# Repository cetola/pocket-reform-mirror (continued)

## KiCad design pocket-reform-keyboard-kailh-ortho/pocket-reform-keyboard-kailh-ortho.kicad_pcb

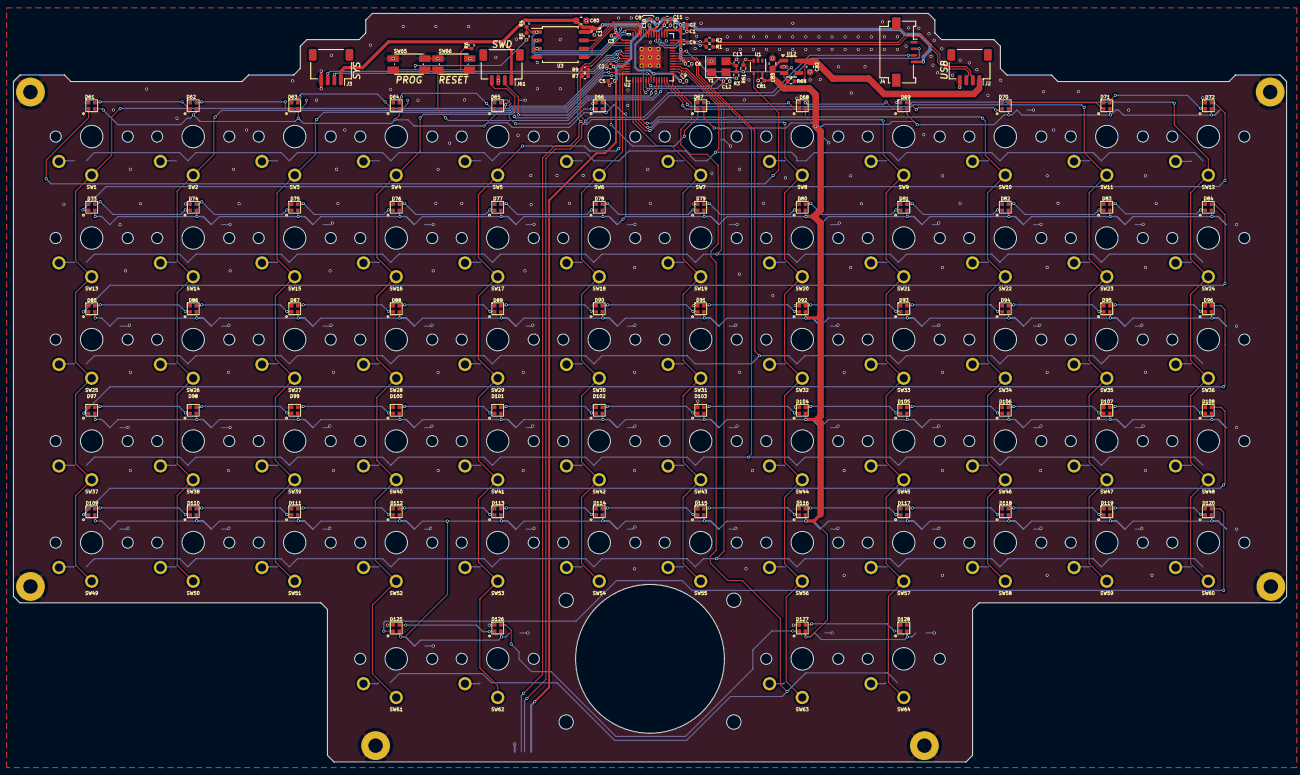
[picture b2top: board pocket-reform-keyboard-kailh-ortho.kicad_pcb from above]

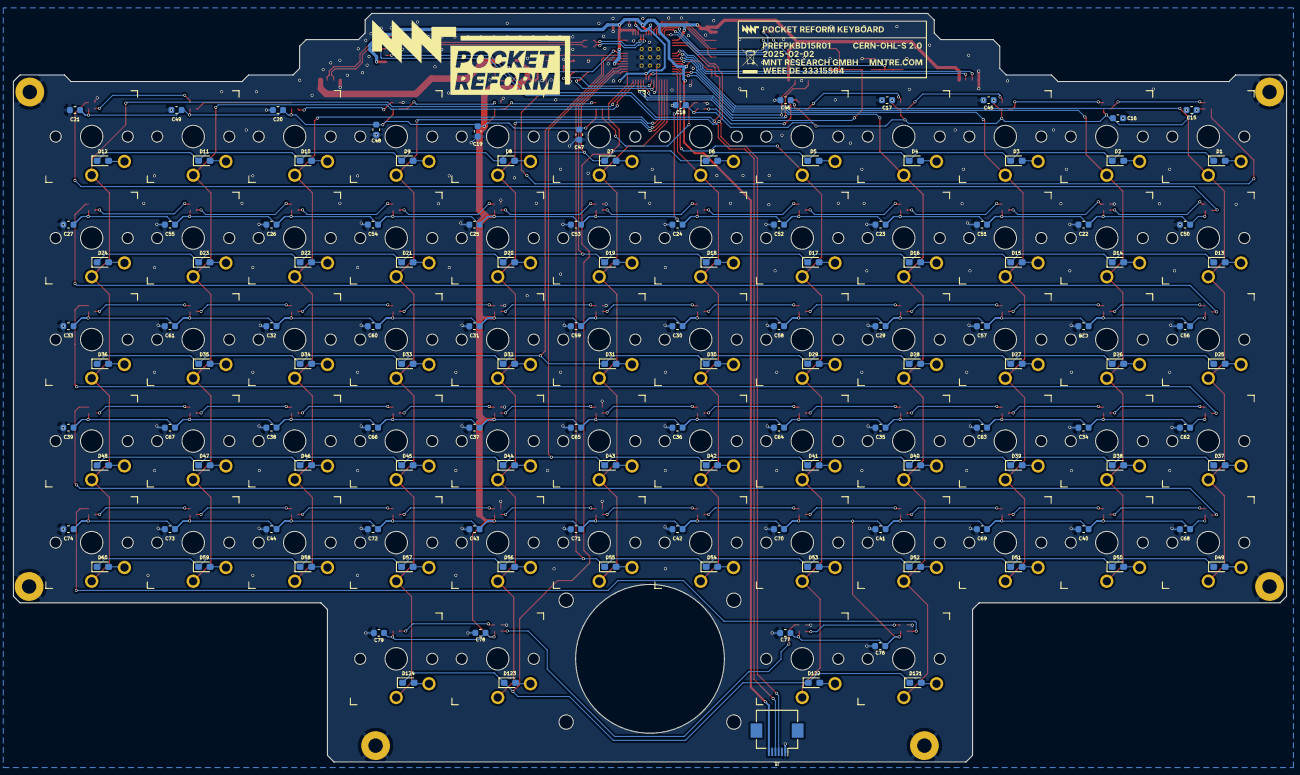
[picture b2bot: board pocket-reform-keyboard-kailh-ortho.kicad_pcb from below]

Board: 4 copper layers, 194.4 x 114.3 mm, 309 parts (131 on the bottom side), 175 nets.

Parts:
C1, C2, C3, C4, C5, C6, C8, C9, C10, C11, C14, C81: 0.1uF; C_0402_1005Metric
C7, C75: 1uF; C_0402_1005Metric
C12, C13: 15pF; C_0402_1005Metric
C15, C16, C17, C18, C19, C20, C21, C22, C23, C24, C25, C26, C27, C28, C29, C30, C31, C32, C33, C34, C35, C36, C37, C38, C39, C40, C41, C42, C43, C44, C45, C46, C47, C48, C49, C50, C51, C52, C53, C54, C55, C56, C57, C58, C59, C60, C61, C62, C63, C64, C65, C66, C67, C68, C69, C70, C71, C72, C73, C74, C76, C77, C78, C79: 0.1uF; C_0603_1608Metric
C80, C82, C83: 10uF; C_0603_1608Metric
D1, D2, D3, D4, D5, D6, D7, D8, D9, D10, D11, D12, D13, D14, D15, D16, D17, D18, D19, D20, D21, D22, D23, D24, D25, D26, D27, D28, D29, D30, D31, D32, D33, D34, D35, D36, D37, D38, D39, D40, D41, D42, D43, D44, D45, D46, D47, D48, D49, D50, D51, D52, D53, D54, D55, D56, D57, D58, D59, D60, D121, D122, D123, D124: MMDL914T1G; D_0603_1608Metric_Pad1.05x0.95mm_HandSolder
D61, D62, D63, D64, D65, D66, D67, D68, D69, D70, D71, D72, D73, D74, D75, D76, D77, D78, D79, D80, D81, D82, D83, D84, D85, D86, D87, D88, D89, D90, D91, D92, D93, D94, D95, D96, D97, D98, D99, D100, D101, D102, D103, D104, D105, D106, D107, D108, D109, D110, D111, D112, D113, D114, D115, D116, D117, D118, D119, D120, D125, D126, D127, D128: SK6805-EC15
GFX1: MNT; pocket-reform
GFX2: MNT; pref-keyboard15-badge
H1: MH1; MountingHole_2.2mm_M2_Pad
H2: MH2; MountingHole_2.2mm_M2_Pad
H3: MH3; MountingHole_2.2mm_M2_Pad
H4: MH4; MountingHole_2.2mm_M2_Pad
H5: MH5; MountingHole_2.2mm_M2_Pad
H6: MH6; MountingHole_2.2mm_M2_Pad
H7, H8, H9, H10: TBH; MountingHole_2.2mm_M2
J1: Conn_01x06_Female; Hirose_FH12-6S-0.5SH_1x06-1MP_P0.50mm_Horizontal
J2: USB; JST_SH_SM04B-SRSS-TB_1x04-1MP_P1.00mm_Horizontal
J3, J61: UART; JST_SH_SM04B-SRSS-TB_1x04-1MP_P1.00mm_Horizontal
J4: AUX; Molex_200528-0040_1x04-1MP_P1.00mm_Horizontal
R1, R2: 27.4; R_0402_1005Metric
R3, R5: 1k; R_0402_1005Metric
R4, R6, R61, R68: 10k; R_0402_1005Metric
R7, R9: 4.7k; R_0402_1005Metric
SW1, SW2, SW3, SW4, SW5, SW6, SW7, SW8, SW9, SW10, SW11, SW12, SW13, SW14, SW15, SW16, SW17, SW18, SW19, SW20, SW21, SW22, SW23, SW24, SW25, SW26, SW27, SW28, SW29, SW30, SW31, SW32, SW33, SW34, SW35, SW36, SW37, SW38, SW39, SW40, SW41, SW42, SW43, SW44, SW45, SW46, SW47, SW48, SW49, SW50, SW51, SW52, SW53, SW54, SW55, SW56, SW57, SW58, SW59, SW60, SW61, SW62, SW63, SW64: Choc; PG1350
SW65: SW_HWB; Diptronics-PTLP2
SW66: SW_RST; Diptronics-PTLP2
U1: SN74LV1T34DCK; SOT-353_SC-70-5
U2: RP2040; RP2040-QFN-56
U3: W25Q32JVSS; SOIC-8_5.23x5.23mm_P1.27mm
U12: AP22815A; SOT-23-5
Y1: 12MHz 12pF; Crystal_SMD_3225-4Pin_3.2x2.5mm

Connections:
+1V1: C9.1, C10.1, C11.1, C75.1, U2.23 (DVDD), U2.45 (VREG_VOUT), U2.50 (DVDD)
+3V3: C1.1, C2.1, C3.1, C4.1, C5.1, C6.1, C7.1, C8.1, C14.1, C80.1, J1.6, J3.1, J4.4, J61.1, R4.1, R6.1, R7.2, R9.2, U2.1 (IOVDD), U2.10 (IOVDD), U2.22 (IOVDD), U2.33 (IOVDD), U2.42 (IOVDD), U2.43 (ADC_AVDD), U2.44 (VREG_IN), U2.48 (USB_VDD), U2.49 (IOVDD), U3.8 (VCC)
+5V: C82.1, J2.1, R68.2, U12.5 (IN)
/Pocket Reform KBD MCU/UD+: R1.2, U2.47 (USB_DP)
/Pocket Reform KBD MCU/UD-: R2.1, U2.46 (USB_DM)
COL1: SW1.1, SW13.1, SW25.1, SW37.1, SW49.1, U2.8 (GPIO6)
COL2: SW2.1, SW14.1, SW26.1, SW38.1, SW50.1, U2.9 (GPIO7)
COL3: SW3.1, SW15.1, SW27.1, SW39.1, SW51.1, U2.11 (GPIO8)
COL4: SW4.1, SW16.1, SW28.1, SW40.1, SW52.1, SW61.1, U2.12 (GPIO9)
COL5: SW5.1, SW17.1, SW29.1, SW41.1, SW53.1, SW62.1, U2.13 (GPIO10)
COL6: SW6.1, SW18.1, SW30.1, SW42.1, SW54.1, U2.14 (GPIO11)
COL7: SW7.1, SW19.1, SW31.1, SW43.1, SW55.1, U2.15 (GPIO12)
COL8: SW8.1, SW20.1, SW32.1, SW44.1, SW56.1, SW63.1, U2.16 (GPIO13)
COL9: SW9.1, SW21.1, SW33.1, SW45.1, SW57.1, SW64.1, U2.17 (GPIO14)
COL10: SW10.1, SW22.1, SW34.1, SW46.1, SW58.1, U2.18 (GPIO15)
COL11: SW11.1, SW23.1, SW35.1, SW47.1, SW59.1, U2.27 (GPIO16)
COL12: SW12.1, SW24.1, SW36.1, SW48.1, SW60.1, U2.28 (GPIO17)
D+: J2.3, R1.1
D-: J2.2, R2.2
GND: C1.2, C2.2, C3.2, C4.2, C5.2, C6.2, C7.2, C8.2, C9.2, C10.2, C11.2, C12.2, C13.2, C14.2, C15.2, C16.2, C17.2, C18.2, C19.2, C20.2, C21.2, C22.2, C23.2, C24.2, C25.2, C26.2, C27.2, C28.2, C29.2, C30.2, C31.2, C32.2, C33.2, C34.2, C35.2, C36.2, C37.2, C38.2, C39.2, C40.2, C41.2, C42.2, C43.2, C44.2, C45.2, C46.2, C47.2, C48.2, C49.2, C50.2, C51.2, C52.2, C53.2, C54.2, C55.2, C56.2, C57.2, C58.2, C59.2, C60.2, C61.2, C62.2, C63.2, C64.2, C65.2, C66.2, C67.2, C68.2, C69.2, C70.2, C71.2, C72.2, C73.2, C74.2, C75.2, C76.2, C77.2, C78.2, C79.2, C80.2, C81.2, C82.2, C83.2, D61.4 (VSS), D62.4 (VSS), D63.4 (VSS), D64.4 (VSS), D65.4 (VSS), D66.4 (VSS), D67.4 (VSS), D68.4 (VSS), D69.4 (VSS), D70.4 (VSS), D71.4 (VSS), D72.4 (VSS), D73.4 (VSS), D74.4 (VSS), D75.4 (VSS), D76.4 (VSS), D77.4 (VSS), D78.4 (VSS), D79.4 (VSS), D80.4 (VSS), D81.4 (VSS), D82.4 (VSS), D83.4 (VSS), D84.4 (VSS), D85.4 (VSS), D86.4 (VSS), D87.4 (VSS), D88.4 (VSS), D89.4 (VSS), D90.4 (VSS), D91.4 (VSS), D92.4 (VSS), D93.4 (VSS), D94.4 (VSS), D95.4 (VSS), D96.4 (VSS), D97.4 (VSS), D98.4 (VSS), D99.4 (VSS), D100.4 (VSS), D101.4 (VSS), D102.4 (VSS), D103.4 (VSS), D104.4 (VSS), D105.4 (VSS), D106.4 (VSS), D107.4 (VSS), D108.4 (VSS), D109.4 (VSS), D110.4 (VSS), D111.4 (VSS), D112.4 (VSS), D113.4 (VSS), D114.4 (VSS), D115.4 (VSS), D116.4 (VSS), D117.4 (VSS), D118.4 (VSS), D119.4 (VSS), D120.4 (VSS), D125.4 (VSS), D126.4 (VSS), D127.4 (VSS), D128.4 (VSS), H1.1, H2.1, H3.1, H4.1, H5.1, H6.1, J1.1, J2.4, J3.4, J4.1, J61.3, R61.1, SW65.2, SW66.2, U1.3 (GND), U2.19 (TESTEN), U2.57 (GND), U3.4 (GND), U12.2 (GND), Y1.2, Y1.4
LED_DATA: U1.2 (A), U2.36 (GPIO24)
LED_POWER: C15.1, C16.1, C17.1, C18.1, C19.1, C20.1, C21.1, C22.1, C23.1, C24.1, C25.1, C26.1, C27.1, C28.1, C29.1, C30.1, C31.1, C32.1, C33.1, C34.1, C35.1, C36.1, C37.1, C38.1, C39.1, C40.1, C41.1, C42.1, C43.1, C44.1, C45.1, C46.1, C47.1, C48.1, C49.1, C50.1, C51.1, C52.1, C53.1, C54.1, C55.1, C56.1, C57.1, C58.1, C59.1, C60.1, C61.1, C62.1, C63.1, C64.1, C65.1, C66.1, C67.1, C68.1, C69.1, C70.1, C71.1, C72.1, C73.1, C74.1, C76.1, C77.1, C78.1, C79.1, C81.1, C83.1, D61.2 (VDD), D62.2 (VDD), D63.2 (VDD), D64.2 (VDD), D65.2 (VDD), D66.2 (VDD), D67.2 (VDD), D68.2 (VDD), D69.2 (VDD), D70.2 (VDD), D71.2 (VDD), D72.2 (VDD), D73.2 (VDD), D74.2 (VDD), D75.2 (VDD), D76.2 (VDD), D77.2 (VDD), D78.2 (VDD), D79.2 (VDD), D80.2 (VDD), D81.2 (VDD), D82.2 (VDD), D83.2 (VDD), D84.2 (VDD), D85.2 (VDD), D86.2 (VDD), D87.2 (VDD), D88.2 (VDD), D89.2 (VDD), D90.2 (VDD), D91.2 (VDD), D92.2 (VDD), D93.2 (VDD), D94.2 (VDD), D95.2 (VDD), D96.2 (VDD), D97.2 (VDD), D98.2 (VDD), D99.2 (VDD), D100.2 (VDD), D101.2 (VDD), D102.2 (VDD), D103.2 (VDD), D104.2 (VDD), D105.2 (VDD), D106.2 (VDD), D107.2 (VDD), D108.2 (VDD), D109.2 (VDD), D110.2 (VDD), D111.2 (VDD), D112.2 (VDD), D113.2 (VDD), D114.2 (VDD), D115.2 (VDD), D116.2 (VDD), D117.2 (VDD), D118.2 (VDD), D119.2 (VDD), D120.2 (VDD), D125.2 (VDD), D126.2 (VDD), D127.2 (VDD), D128.2 (VDD), U1.5 (VCC), U12.1 (OUT)
LED_PWR_EN: R61.2, U2.37 (GPIO25), U12.4 (EN)
unnamed: C13.1, R3.1, Y1.3
unnamed: D1.2 (A), SW1.2
unnamed: D2.2 (A), SW2.2
unnamed: D3.2 (A), SW3.2
unnamed: D4.2 (A), SW4.2
unnamed: D5.2 (A), SW5.2
unnamed: D6.2 (A), SW6.2
unnamed: D7.2 (A), SW7.2
unnamed: D8.2 (A), SW8.2
unnamed: D9.2 (A), SW9.2
unnamed: D10.2 (A), SW10.2
unnamed: D11.2 (A), SW11.2
unnamed: D12.2 (A), SW12.2
unnamed: D13.2 (A), SW13.2
unnamed: D14.2 (A), SW14.2
unnamed: D15.2 (A), SW15.2
unnamed: D16.2 (A), SW16.2
unnamed: D17.2 (A), SW17.2
unnamed: D18.2 (A), SW18.2
unnamed: D19.2 (A), SW19.2
unnamed: D20.2 (A), SW20.2
unnamed: D21.2 (A), SW21.2
unnamed: D22.2 (A), SW22.2
unnamed: D23.2 (A), SW23.2
unnamed: D24.2 (A), SW24.2
unnamed: D25.2 (A), SW25.2
unnamed: D26.2 (A), SW26.2
unnamed: D27.2 (A), SW27.2
unnamed: D28.2 (A), SW28.2
unnamed: D29.2 (A), SW29.2
unnamed: D30.2 (A), SW30.2
unnamed: D31.2 (A), SW31.2
unnamed: D32.2 (A), SW32.2
unnamed: D33.2 (A), SW33.2
unnamed: D34.2 (A), SW34.2
unnamed: D35.2 (A), SW35.2
unnamed: D36.2 (A), SW36.2
unnamed: D37.2 (A), SW37.2
unnamed: D38.2 (A), SW38.2
unnamed: D39.2 (A), SW39.2
unnamed: D40.2 (A), SW40.2
unnamed: D41.2 (A), SW41.2
unnamed: D42.2 (A), SW42.2
unnamed: D43.2 (A), SW43.2
unnamed: D44.2 (A), SW44.2
unnamed: D45.2 (A), SW45.2
unnamed: D46.2 (A), SW46.2
unnamed: D47.2 (A), SW47.2
unnamed: D48.2 (A), SW48.2
unnamed: D49.2 (A), SW49.2
unnamed: D50.2 (A), SW50.2
unnamed: D51.2 (A), SW51.2
unnamed: D52.2 (A), SW52.2
unnamed: D53.2 (A), SW53.2
unnamed: D54.2 (A), SW54.2
unnamed: D55.2 (A), SW55.2
unnamed: D56.2 (A), SW56.2
unnamed: D57.2 (A), SW57.2
unnamed: D58.2 (A), SW58.2
unnamed: D59.2 (A), SW59.2
unnamed: D60.2 (A), SW60.2
unnamed: D61.1 (DIN), U1.4 (Y)
unnamed: D61.3 (DOUT), D62.1 (DIN)
unnamed: D62.3 (DOUT), D63.1 (DIN)
unnamed: D63.3 (DOUT), D64.1 (DIN)
unnamed: D64.3 (DOUT), D65.1 (DIN)
unnamed: D65.3 (DOUT), D66.1 (DIN)
unnamed: D66.3 (DOUT), D67.1 (DIN)
unnamed: D67.3 (DOUT), D68.1 (DIN)
unnamed: D68.3 (DOUT), D69.1 (DIN)
unnamed: D69.3 (DOUT), D70.1 (DIN)
unnamed: D70.3 (DOUT), D71.1 (DIN)
unnamed: D71.3 (DOUT), D72.1 (DIN)
unnamed: D72.3 (DOUT), D73.1 (DIN)
unnamed: D73.3 (DOUT), D74.1 (DIN)
unnamed: D74.3 (DOUT), D75.1 (DIN)
unnamed: D75.3 (DOUT), D76.1 (DIN)
unnamed: D76.3 (DOUT), D77.1 (DIN)
unnamed: D77.3 (DOUT), D78.1 (DIN)
unnamed: D78.3 (DOUT), D79.1 (DIN)
unnamed: D79.3 (DOUT), D80.1 (DIN)
unnamed: D80.3 (DOUT), D81.1 (DIN)
unnamed: D81.3 (DOUT), D82.1 (DIN)
unnamed: D82.3 (DOUT), D83.1 (DIN)
unnamed: D83.3 (DOUT), D84.1 (DIN)
unnamed: D84.3 (DOUT), D85.1 (DIN)
unnamed: D85.3 (DOUT), D86.1 (DIN)
unnamed: D86.3 (DOUT), D87.1 (DIN)
unnamed: D87.3 (DOUT), D88.1 (DIN)
unnamed: D88.3 (DOUT), D89.1 (DIN)
unnamed: D89.3 (DOUT), D90.1 (DIN)
unnamed: D90.3 (DOUT), D91.1 (DIN)
unnamed: D91.3 (DOUT), D92.1 (DIN)
unnamed: D92.3 (DOUT), D93.1 (DIN)
unnamed: D93.3 (DOUT), D94.1 (DIN)
unnamed: D94.3 (DOUT), D95.1 (DIN)
unnamed: D95.3 (DOUT), D96.1 (DIN)
unnamed: D96.3 (DOUT), D97.1 (DIN)
unnamed: D97.3 (DOUT), D98.1 (DIN)
unnamed: D98.3 (DOUT), D99.1 (DIN)
unnamed: D99.3 (DOUT), D100.1 (DIN)
unnamed: D100.3 (DOUT), D101.1 (DIN)
unnamed: D101.3 (DOUT), D102.1 (DIN)
unnamed: D102.3 (DOUT), D103.1 (DIN)
unnamed: D103.3 (DOUT), D104.1 (DIN)
unnamed: D104.3 (DOUT), D105.1 (DIN)
unnamed: D105.3 (DOUT), D106.1 (DIN)
unnamed: D106.3 (DOUT), D107.1 (DIN)
unnamed: D107.3 (DOUT), D108.1 (DIN)
unnamed: D108.3 (DOUT), D109.1 (DIN)
unnamed: D109.3 (DOUT), D110.1 (DIN)
unnamed: D110.3 (DOUT), D111.1 (DIN)
unnamed: D111.3 (DOUT), D112.1 (DIN)
unnamed: D112.3 (DOUT), D113.1 (DIN)
unnamed: D113.3 (DOUT), D114.1 (DIN)
unnamed: D114.3 (DOUT), D115.1 (DIN)
unnamed: D115.3 (DOUT), D116.1 (DIN)
unnamed: D116.3 (DOUT), D117.1 (DIN)
unnamed: D117.3 (DOUT), D118.1 (DIN)
unnamed: D118.3 (DOUT), D119.1 (DIN)
unnamed: D119.3 (DOUT), D120.1 (DIN)
unnamed: D120.3 (DOUT), D125.1 (DIN)
unnamed: D121.2 (A), SW61.2
unnamed: D122.2 (A), SW62.2
unnamed: D123.2 (A), SW63.2
unnamed: D124.2 (A), SW64.2
unnamed: D125.3 (DOUT), D126.1 (DIN)
unnamed: D126.3 (DOUT), D127.1 (DIN)
unnamed: D127.3 (DOUT), D128.1 (DIN)
unnamed: C12.1, U2.20 (XIN), Y1.1
unnamed: R3.2, U2.21 (XOUT)
unnamed: R68.1, U12.3 (FLG)
PROG: R5.1, SW65.1
QSPI_CS: R4.2, R5.2, U2.56 (QSPI_SS), U3.1 (~CS)
QSPI_SCK: U2.52 (QSPI_SCLK), U3.6 (CLK)
QSPI_SD0: U2.53 (QSPI_SD0), U3.5 (DI(IO0))
QSPI_SD1: U2.55 (QSPI_SD1), U3.2 (DO(IO1))
QSPI_SD2: U2.54 (QSPI_SD2), U3.3 (IO2)
QSPI_SD3: U2.51 (QSPI_SD3), U3.7 (IO3)
RESET: R6.2, SW66.1, U2.26 (RUN)
ROW1: D1.1 (K), D2.1 (K), D3.1 (K), D4.1 (K), D5.1 (K), D6.1 (K), D7.1 (K), D8.1 (K), D9.1 (K), D10.1 (K), D11.1 (K), D12.1 (K), U2.30 (GPIO19)
ROW2: D13.1 (K), D14.1 (K), D15.1 (K), D16.1 (K), D17.1 (K), D18.1 (K), D19.1 (K), D20.1 (K), D21.1 (K), D22.1 (K), D23.1 (K), D24.1 (K), U2.31 (GPIO20)
ROW3: D25.1 (K), D26.1 (K), D27.1 (K), D28.1 (K), D29.1 (K), D30.1 (K), D31.1 (K), D32.1 (K), D33.1 (K), D34.1 (K), D35.1 (K), D36.1 (K), U2.35 (GPIO23)
ROW4: D37.1 (K), D38.1 (K), D39.1 (K), D40.1 (K), D41.1 (K), D42.1 (K), D43.1 (K), D44.1 (K), D45.1 (K), D46.1 (K), D47.1 (K), D48.1 (K), U2.34 (GPIO22)
ROW5: D49.1 (K), D50.1 (K), D51.1 (K), D52.1 (K), D53.1 (K), D54.1 (K), D55.1 (K), D56.1 (K), D57.1 (K), D58.1 (K), D59.1 (K), D60.1 (K), U2.32 (GPIO21)
ROW6: D121.1 (K), D122.1 (K), D123.1 (K), D124.1 (K), U2.29 (GPIO18)
SCL: J1.4, J4.3, R7.1, U2.3 (GPIO1)
SDA: J1.3, J4.2, R9.1, U2.2 (GPIO0)
SWC: J61.2, U2.24 (SWCLK)
SWD: J61.4, U2.25 (SWD)
UART_RX: J3.2, U2.7 (GPIO5)
UART_TX: J3.3, U2.6 (GPIO4)

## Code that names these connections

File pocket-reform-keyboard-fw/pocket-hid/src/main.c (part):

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  uart_set_format(UART_ID, DATA_BITS, STOP_BITS, PARITY);
  uart_set_hw_flow(UART_ID, false, false);
  uart_set_fifo_enabled(UART_ID, true);
  gpio_set_function(PIN_UART_TX, GPIO_FUNC_UART);
  gpio_set_function(PIN_UART_RX, GPIO_FUNC_UART);
  unsigned int UART_IRQ = UART_ID == uart0 ? UART0_IRQ : UART1_IRQ;

  gpio_init(PIN_LEDS);
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
  /* Configure rows as input and enable pull-downs */
  gpio_init_mask(PIN_ROW_MASK);
  gpio_pull_down(PIN_ROW1);
  gpio_pull_down(PIN_ROW2);
  gpio_pull_down(PIN_ROW3);
  gpio_pull_down(PIN_ROW4);
  gpio_pull_down(PIN_ROW5);
  gpio_pull_down(PIN_ROW6);

  i2c_init(i2c0, 400 * 1000);
  gpio_set_function(PIN_SDA, GPIO_FUNC_I2C);
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    uint32_t rows = 0;

    switch (x) {
    case 0: gpio_put(PIN_COL1, 1); break;
    case 1: gpio_put(PIN_COL2, 1); break;
    case 2: gpio_put(PIN_COL3, 1); break;
    case 3: gpio_put(PIN_COL4, 1); break;
    case 4: gpio_put(PIN_COL5, 1); break;
    case 5: gpio_put(PIN_COL6, 1); break;
    case 6: gpio_put(PIN_COL7, 1); break;
    case 7: gpio_put(PIN_COL8, 1); break;
    case 8: gpio_put(PIN_COL9, 1); break;
    case 9: gpio_put(PIN_COL10, 1); break;
    case 10: gpio_put(PIN_COL11, 1); break;
    case 11: gpio_put(PIN_COL12, 1); break;
    }

    // wait for signal to stabilize
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      uint8_t debounced_pressed = 0;

      switch (y) {
      case 0:  pressed = (rows & (1u<<PIN_ROW1)) != 0; break;
      case 1:  pressed = (rows & (1u<<PIN_ROW2)) != 0; break;
      case 2:  pressed = (rows & (1u<<PIN_ROW3)) != 0; break;
      case 3:  pressed = (rows & (1u<<PIN_ROW4)) != 0; break;
      case 4:  pressed = (rows & (1u<<PIN_ROW5)) != 0; break;
      case 5:  pressed = (rows & (1u<<PIN_ROW6)) != 0; break;
      }

      // shift new state as bit into debounce "register"
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
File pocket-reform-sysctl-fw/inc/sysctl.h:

#ifndef _POCKET_SYSCTL_H
#define _POCKET_SYSCTL_H

#include <stdint.h>

#include "pico/stdlib.h"
#include "pico/binary_info.h"
#include "hardware/i2c.h"
#include "hardware/spi.h"
#include "hardware/irq.h"
#include "hardware/rtc.h"
#include "hardware/clocks.h"
#include "hardware/pwm.h"
#include "hardware/watchdog.h"
#include "hardware/structs/watchdog.h"
#include "hardware/structs/vreg_and_chip_reset.h"

// #define OTG_AS_5V // WARNING: defining this requires the hardware mod described in https://source.mnt.re/reform/pocket-reform/-/issues/3
// #define FACTORY_MODE // turn device on immediately after starting sysctl
#define ACM_ENABLED // usb serial control for debugging

#define FW_STRING1 "PREF1SYS"
#define FW_STRING2 "R1"

#define PIN_SDA 0
#define PIN_SCL 1

#define PIN_DISP_RESET 2
#define PIN_FLIGHTMODE 3
#define PIN_KBD_UART_TX 4
#define PIN_KBD_UART_RX 5
#define PIN_WOWWAN 6
// TODO: FIXME: DISP_2_PWM on v20
#define PIN_DISP_EN 7
#define PIN_SOM_MOSI 8
#define PIN_SOM_SS0 9
#define PIN_SOM_SCK 10
#define PIN_SOM_MISO 11
#define PIN_SOM_UART_TX 12
#define PIN_SOM_UART_RX 13
#define PIN_FUSB_INT 14
#define PIN_LED_B 15
#define PIN_LED_B_PWM_SLICE 7
#define PIN_LED_B_PWM_CHAN PWM_CHAN_B
#define PIN_LED_R 16
#define PIN_LED_R_PWM_SLICE 0
#define PIN_LED_R_PWM_CHAN PWM_CHAN_A
#define PIN_LED_G 17
#define PIN_MODEM_POWER 18
#define PIN_SOM_WAKE 19
#define PIN_MODEM_RESET 20
#define PIN_1V1_ENABLE 23
// 3V3_ENABLE on v10, kickstart (power on button) DP HPD output on v20
#define PIN_3V3_ENABLE 24
#define PIN_V20_DP_HPD 24
// 5V_ENABLE on v10, kickstart (power on button) input on v20
#define PIN_5V_ENABLE 25
#define PIN_PHONE_DPR 27
// USB_SRC/PWREN_LATCH on v10, USB_SRC1/USB_SRC2 on v20
#define PIN_USB_SRC_ENABLE 28
#define PIN_USB_SRC1_ENABLE 28
#define PIN_PWREN_LATCH 29
#define PIN_USB_SRC2_ENABLE 29
// NC on v10, EDL/USB bootloader enable on v20
#define PIN_USB_LOADER_SW 26

// FUSB302B USB-PD controller
#define FUSB_ADDR 0x22
// MAX17320 protector/balancer
// https://datasheets.maximintegrated.com/en/ds/MAX17320.pdf
#define MAX_ADDR1 0x36
#define MAX_ADDR2 0x0b
// MP2650 charger
// https://www.monolithicpower.com/en/documentview/productdocument/index/version/2/document_type/Datasheet/lang/en/sku/MP2650GV/document_id/9664/
#define MPS_ADDR 0x5c
#define TMUX_ADDR 0x54
// PCA9536DP GPIO extender (for USWITCHes)
#define PCA9536_ADDR 0x41
// PCA9557PW GPIO extender
#define PCA9557_ADDR 0x19
// TODO eeprom: 0x50/0x58

#define I2C_TIMEOUT (1000 * 20)

#define UART_ID uart1
#define BAUD_RATE 115200
#define DATA_BITS 8
#define STOP_BITS 1
#define PARITY UART_PARITY_NONE

#define BOOT_MAGIC_2 0xAA55F0F0
#define BOOT_MAGIC_3 0x0F0F55AA
#define BOOT_MAGIC_OFF (io_rw_32)(-1)
// for remembering critical settings across warm resets
#define BOOT_SCRATCH_BITS0_IDX 1
// if this bit is set, we assume display v2 (for display_v2_backlight_function)
#define BOOT_SCRATCH_BITS0_DISPV2 (1<<0)

#define BATTERY_CAPACITY_MILLIAMP_HOURS 4000

#include "pd_com.h"

typedef struct battery_info_s
{
  bool som_is_powered;

  // reported by charger
  float battery_volts;
  float battery_amps;
  float input_volts;
  int cell_max_mah;

  // reported by balancer
  float cell1_volts;
  float cell2_volts;
  int charge_percentage;
  float time_to_empty;
  float gauge_avg_milliamps;
  float gauge_vpack;

  // metadata
  bool emergency_charge_necessary;
  bool print_pack_info;
  uint16_t max17320_devname;
  uint16_t ticks;
} battery_info_s;

#include "fusb302b.h"
#include "pd.h"
#include "max17320.h"
#include "mp2650.h"
#include "ext_gpio.h"

// Shared functions with communication classes
int mb_version();
void som_wake();
void turn_som_power_on();
void turn_som_power_off();
void set_display_v2_backlight_unlock(int on);
void set_display_backlight(int percent);
void set_display_backlight_freq(int freq);

void usb_host_5v_set(int port, int enable);
void set_usb_mode(int port, int mode);
void charger_enable_charge(int current);
void charger_disable_charge();
void enter_powersave(void);

// Recommended to call these around any i2c transactions
void sysctl_enable_irqs();
void sysctl_disable_irqs();

#endif

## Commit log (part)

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2026-04-10 WIP: mainboard2.0 support incl displayport alt-mode sketch
2026-04-10 add key-value store sketch with SPI interface; add mb2.0 usb mux SPI interface
2026-04-10 add .clang-format; format src/uart_com.c
2026-04-10 WIP: kv store implementation for uart interface
2026-04-29 feat: add hid wbio command for sending bitmap to oled
    Apply https://source.mnt.re/reform/reform/-/merge_requests/98 to pocket
    reform.
2026-05-03 WIP sc-fw: sketch of simple cli parser
2026-05-08 fixup for anri's layout
2026-05-08 SC: fix bools
2026-05-08 SC: cli: make it build
2026-05-08 WIP: SC: add compile_flags.txt for eglot/clangd
2026-05-08 SC: WIP cli test/harness
2026-05-09 WIP: SC: cli: working function call
2026-05-09 WIP: SC: wire up CLI to HWAPI and USB ACM commands
2026-05-11 SC: reformat codebase (whitespace etc), add editorconfig
2026-05-11 SC: debug the CLI over uart, voltage reporting and rail toggling works
2026-05-12 SC: change spi handling to CS interrupt driven, improve timing (works)
2026-05-12 SC: manage CLI instance per i/o (spi,uart,usb); legacy kbd api compat
2026-05-12 SC: don't debug by default
2026-05-12 SC: compile_flags: fixup includes
2026-05-12 SC: vars and units fixes, void funcs
2026-06-02 sysctl/cli: add basic line editor for usb, add more convenient usb modes
2026-06-05 sysctl-fw: extended support for soc suspend/wake
2026-06-05 sc: make backlight pwm freq editable
2026-06-19 sc: fix set-usb arity
2026-06-19 sc: WIP: implement switches for mb2 vs 1
2026-06-19 sc: WIP: implement switches for mb2 in pd_com
2026-06-19 sc: WIP: implement switches for mb2 in hwapi_pocket
2026-06-19 kbd-fw: add basic console interaction with system controller CLI on OLED
2026-06-27 WIP alt mode hacking
2026-06-27 WIP local alt mode hacking
2026-06-27 WIP hacking: fix syscon warm boot after update
2026-06-27 WIP fix usb mux default config after warm boot/fw update
2026-06-27 WIP DP alt-mode: monitor turns on!
2026-06-28 WIP PD hacking
2026-06-29 WIP sysctl: handle a lot of missing SRC states; several usb-c alt-mode adapters work now
2026-06-30 sysctl: fix whitespace; support HPD output for DP alt-mode
2026-06-30 sysctl usb-c DP WIP: xreal pro and apple hdmi adapter work with some wiggling
2026-06-30 mb2.0: snapshot before rev2
2026-06-30 mainboard: 2.0 R-1 schematic with USB and DP fixes
2026-06-30 mainboard 2.0 r-1 polished
2026-06-30 mb2.0: component updates

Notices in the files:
pocket-reform-keyboard-fw/pocket-hid/src/main.c:
SPDX-License-Identifier: GPL-3.0-or-later
Copyright 2021-2025 MNT Research GmbH (mntre.com)
Copyright 2019 Ha Thach (tinyusb.org)
